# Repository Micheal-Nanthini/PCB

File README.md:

View this project on [CADLAB.io](https://cadlab.io/project/29278). 

# PCB

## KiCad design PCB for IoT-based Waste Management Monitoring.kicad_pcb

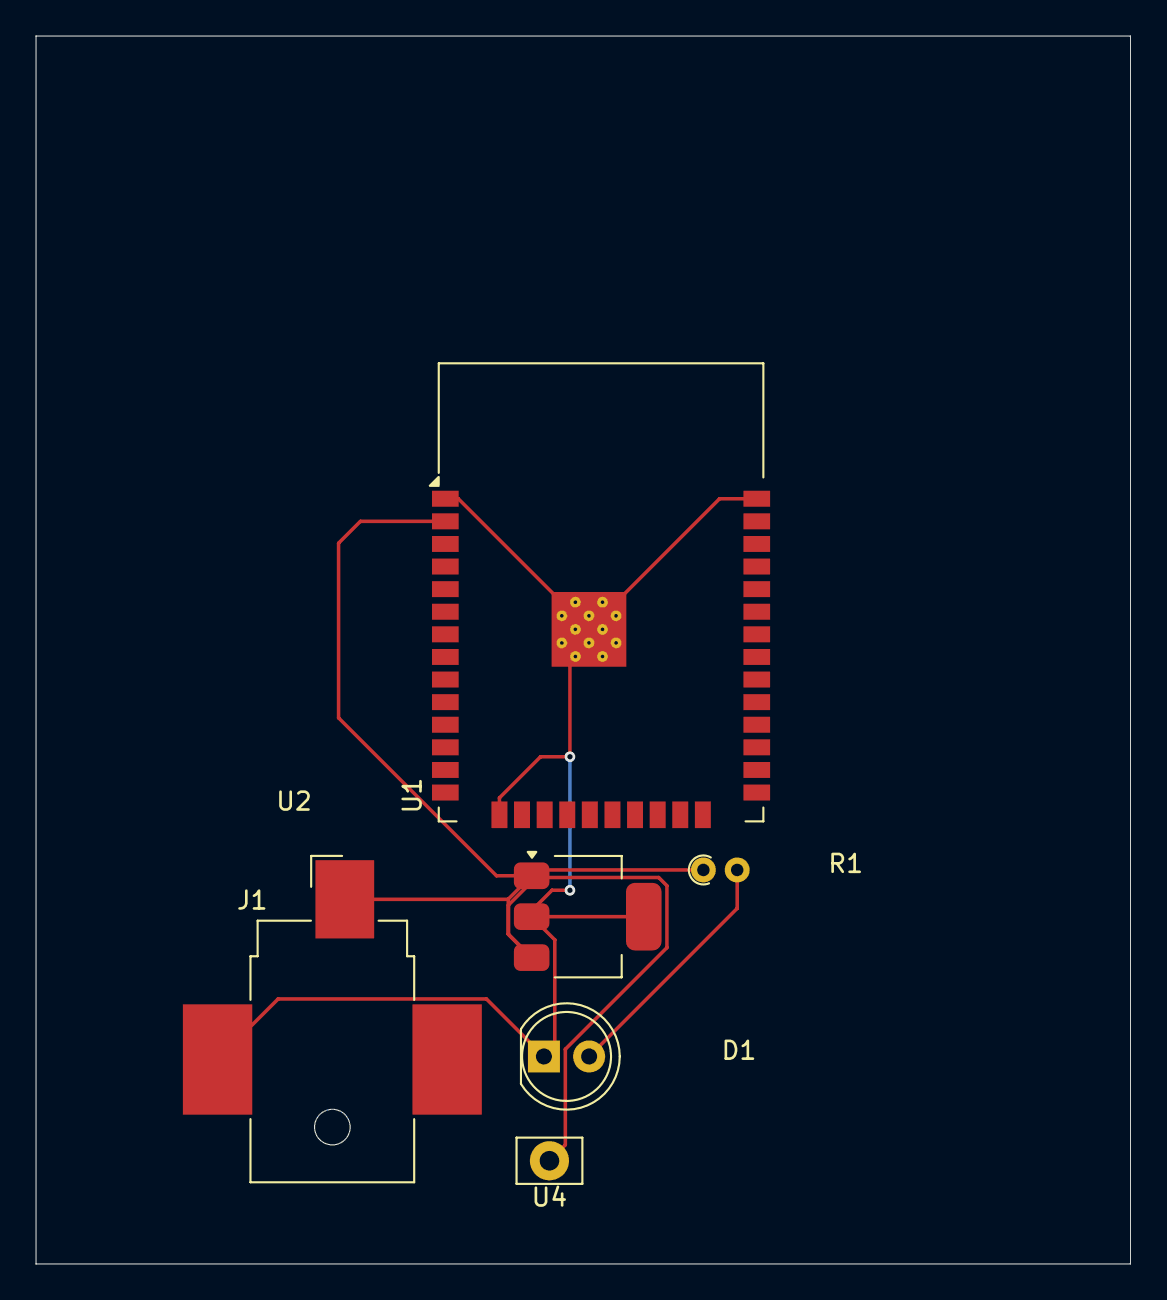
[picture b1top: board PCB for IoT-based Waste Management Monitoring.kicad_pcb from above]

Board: 2 copper layers, 61.5 x 69.0 mm, 6 parts (0 on the bottom side), 3 nets.

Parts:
D1: LED; LED_D5.0mm
J1: Jack-DC; BarrelJack_CUI_PJ-036AH-SMT_Horizontal
R1: R; R_Axial_DIN0204_L3.6mm_D1.6mm_P1.90mm_Vertical
U1: ESP32-WROOM-32
U2: AMS1117; SOT-223-3_TabPin2
U4: HC-SR04; Pin_D1.1mm_L10.2mm_W3.5mm_Flat

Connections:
+5V: J1.1, R1.1, U1.2 (VDD), U2.1 (ADJ), U2.3 (VI), U4.1 (VCC)
GND: D1.1 (K), J1.2, U1.1 (GND), U1.15 (GND), U1.38 (GND), U1.39 (GND), U2.2 (VO)
unnamed: D1.2 (A), R1.2

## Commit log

2025-04-19 Backlink to CADLAB.io has been added.
